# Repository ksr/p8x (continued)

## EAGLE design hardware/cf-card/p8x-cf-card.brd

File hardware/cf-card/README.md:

# CF-IDE Card

> **Theory of operation:** [p8x-cf-card-theory.md](p8x-cf-card-theory.md) — deep walkthrough of inputs/outputs, signal flow, and logic.

Adds mass storage: a CompactFlash card running in **8-bit True IDE mode**,
memory-mapped into the I/O page at **$FF10–$FF17**. This is what lets the P8X load
an OS and a filesystem from removable media instead of living entirely in ROM.

> **Rev B (2026-09-19): two drives.** The routed KiCad board in
> [`kicad/`](kicad/README.md) (not yet fabricated) carries a second, fully decoded
> CF drive: drive 0 at `$FF10–$FF17` on header J2, drive 1 at `$FF18–$FF1F` on
> header J5, each with its own 74245 buffer, strobe glue, pull-ups and activity
> LED (master/slave on one channel was rejected as unreliable for True IDE CF).
> **Software follow-up:** the firmware CF driver and the emulator select drive 1
> with the device bit on `$FF10–$FF17`, so drive 1 on this card needs a
> drive-selectable port base first; drive 0 works unchanged. The chip-by-chip text
> below describes the drive-0 circuit.

> This README describes the circuit as actually built in
> [`generators/gen_eagle.py`](../../generators/gen_eagle.py). For the storage
> software stack see [p8x-cf-os-design.md](p8x-cf-os-design.md) and
> [p8xfs-v2-hierarchical.md](p8xfs-v2-hierarchical.md); for bus pins see
> [p8x-bus-definition.md](../backplane/p8x-bus-definition.md).

## Chip inventory

| Ref | Device | Role |
|-----|--------|------|
| U1 | 74245 | Bidirectional data-bus transceiver (P8X bus ↔ CF data) |
| U2 | 7430 | 8-input NAND — I/O page ($FFxx) detector |
| U3 | 74138 | DOE decoder (read enable) |
| U4 | 74138 | DLD decoder (write strobe) |
| U5 | 74HCT14 | Schmitt inverters — strobe/select conditioning |
| U6, U7 | 7410 | 3-input NAND — register/select decode and -IOR/-IOW gating |
| U8 | 74HCT08 | AND glue — chip-select combine, activity LED |
| J2 | 40-pin IDE | CompactFlash / IDE connector |

## How it works

### Address decode ($FF10–$FF17)
U2 (7430) detects the `$FFxx` page. The CF task-file registers occupy
`$FF10–$FF17`; the low address lines A0–A4 select the individual IDE register, and
the 7410 NANDs (U6/U7) combine the page hit with A3/A4 to produce the two True-IDE
chip selects **-CS0** (command block) and **-CS1** (control block). U8 ANDs them
into a single `-CFSEL` "this card is addressed" signal.

### Read / write strobes
DOE code 7 (`-RD`) and DLD code 7 (`-MEMW`) are decoded by U3/U4. Gated with the
clock and `-CFSEL` through U5/U7, they become the IDE bus strobes **-IOR** (I/O
read) and **-IOW** (I/O write) on the connector. These are the standard True-IDE
timing signals the CF card expects.

### Data path
A single **74245** (U1) bridges the P8X data bus and the CF data lines (the low 8
bits — this is 8-bit mode, so the high byte of the IDE 16-bit data path is unused).
Its **direction** follows `-IOR` (read = drive toward the P8X bus) and it is
**enabled** only when the card is selected (`-CFOE`), so it never contends with
other bus drivers.

### Status lines
The CF's open-drain status lines — **IORDY**, **-PDIAG**, **-DASP** — are pulled up
through a SIP resistor network (RN1). `-DASP` (drive active / slave present) also
drives the activity LED.

### Reset
The backplane **-RES** is wired to the IDE connector's reset pin, so the CF card is
reset together with the rest of the machine.

## Bus codes this card owns
- **DOE:** 7 = read (drives D0–D7 when `$FF10–$FF17` is addressed)
- **DLD:** 7 = write (`MEMW`) — shared decode convention with memory & I/O cards

The CF card, memory card, and I/O card all decode the same DOE=7 / DLD=7 codes;
the address decode (which page/region) is what keeps exactly one of them active per
cycle.

## LEDs
PWR (green), ACT (yellow — card selected / access in progress), DASP (green — CF
present and active).

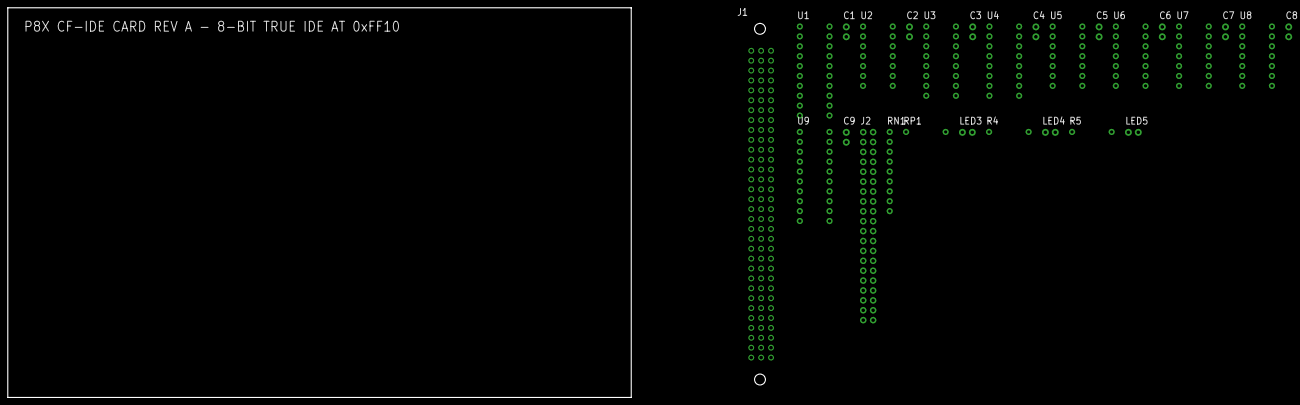
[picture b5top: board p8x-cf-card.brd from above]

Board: 4 copper layers, 160.0 x 100.0 mm, 27 parts (0 on the bottom side), 70 nets, no tracks yet.

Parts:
C1, C2, C3, C4, C5, C6, C7, C8, C9: 100nF; C_DISC1
J1: MABC96R
J2: IDE-40; HDR40
LED3, LED5: GRN; LED5
LED4: YEL; LED5
R4: 1K; R_AXIAL
R5: 330R; R_AXIAL
RN1: 8X10K; SIP9
RP1: 1K; R_AXIAL
U1: 74HCT245; DIP20
U2: 74HCT30; DIP14
U3, U4: 74HCT138; DIP16
U5: 74HCT14; DIP14
U6, U7: 74HCT10; DIP14
U8: 74HCT08; DIP14
U9: 74HCT374; DIP20

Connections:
-CFOE: U1.19, U8.6, U8.9, U8.10
-CFSEL: U5.11, U8.3
-CS0: J2.37, U6.12, U8.1
-CS1: J2.38, U6.6, U8.2
-DASP: J2.39, LED5.1, RN1.4
-IOR: J2.25, U1.1, U7.12, U8.4
-IOW: J2.23, U7.6, U8.5
-MEMW: U4.7, U5.5
-PDIAG: J2.34, RN1.3
-RD: U3.7, U5.3
-RES: J1.A11, J2.1
A0: J1.C3, J2.35
A1: J1.C4, J2.33
A2: J1.C5, J2.36
A3: J1.C6, U5.9, U6.5
A3N: U5.8, U6.13
A4: J1.C7, U6.2, U6.4
A8: J1.C11, U2.1
A9: J1.C12, U2.2
A10: J1.C13, U2.3
A11: J1.C14, U2.4
A12: J1.C15, U2.5
A13: J1.C16, U2.6
A14: J1.C17, U2.11
A15: J1.C18, U2.12
ACTK: LED4.1, U8.8
CFD0: J2.17, U1.18
CFD1: J2.15, U1.17
CFD2: J2.13, U1.16
CFD3: J2.11, U1.15
CFD4: J2.9, U1.14
CFD5: J2.7, U1.13
CFD6: J2.5, U1.12
CFD7: J2.3, U1.11
CFD8: J2.4, U9.3
CFD9: J2.6, U9.4
CFD10: J2.8, U9.7
CFD11: J2.10, U9.8
CFD12: J2.12, U9.13
CFD13: J2.14, U9.14
CFD14: J2.16, U9.17
CFD15: J2.18, U9.18
CLKB: J1.A25, U7.5, U7.13
D0: J1.A3, U1.2
D1: J1.A4, U1.3
D2: J1.A5, U1.4
D3: J1.A6, U1.5
D4: J1.A7, U1.6
D5: J1.A8, U1.7
D6: J1.A9, U1.8
D7: J1.A10, U1.9
DLD0: J1.A16, U4.1
DLD1: J1.A17, U4.2
DLD2: J1.A18, U4.3
DLD3: J1.A19, U4.4
DOE0: J1.A12, U3.1
DOE1: J1.A13, U3.2
DOE2: J1.A14, U3.3
DOE3: J1.A15, U3.4
GND: C1.2, C2.2, C3.2, C4.2, C5.2, C6.2, C7.2, C8.2, C9.2, J1.A31, J1.A32, J1.B3, J1.B5, J1.B7, J1.B9, J1.B11, J1.B13, J1.B15, J1.B17, J1.B19, J1.B21, J1.B23, J1.B25, J1.B31, J1.B32, J1.C31, J1.C32, J2.2, J2.19, J2.22, J2.24, J2.26, J2.28, J2.30, J2.40, LED3.1, U1.10, U2.7, U3.5, U3.8, U4.5, U4.8, U5.7, U5.13, U6.7, U6.9, U6.10, U6.11, U7.7, U7.9, U7.10, U7.11, U8.7, U8.12, U8.13, U9.10, U9.11
IOPG: U2.8, U5.1
IOPGP: U5.2, U6.1, U6.3
IORDY: J2.27, RN1.2
LEDAC: LED4.2, R4.2
LEDDA: LED5.2, R5.2
LEDP: LED3.2, RP1.2
RDP: U5.4, U7.2
SELP: U5.10, U7.1, U7.3
VCC: C1.1, C2.1, C3.1, C4.1, C5.1, C6.1, C7.1, C8.1, C9.1, J1.A1, J1.A2, J1.B1, J1.B2, J1.C1, J1.C2, J2.29, R4.1, R5.1, RN1.1, RP1.1, U1.20, U2.14, U3.6, U3.16, U4.6, U4.16, U5.14, U6.14, U7.14, U8.14, U9.1, U9.20
WRP: U5.6, U7.4

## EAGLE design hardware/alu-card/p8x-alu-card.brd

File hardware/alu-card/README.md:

# ALU Card

> **Theory of operation:** [p8x-alu-card-theory.md](p8x-alu-card-theory.md) — deep walkthrough of inputs/outputs, signal flow, and logic.

Holds the two ALU operand registers (**A**, **B**), the two hidden microcode
temporaries (**T**, **T2**), the **74181-based ALU** with a post-ALU shifter, and
the **FLAGS** register. All arithmetic and logic happens here.

> This README describes the circuit as actually built in
> [`generators/gen_eagle.py`](../../generators/gen_eagle.py). See
> [p8x-system-design.md §5](../../docs/p8x-system-design.md) for the overview and
> [p8x-bus-definition.md](../backplane/p8x-bus-definition.md) for bus pins.

## Chip inventory

| Ref | Device | Role |
|-----|--------|------|
| U1, U2 | 74377 + 74244 | A register (load latch + bus-drive buffer) |
| U3, U4 | 74377 + 74244 | B register |
| U5, U6 | 74377 + 74244 | T register (hidden temp) |
| U7, U8 | 74377 + 74244 | T2 register (hidden temp) |
| U9, U10 | 74181 | ALU, low and high nibble |
| U11 | 74182 | Carry-lookahead generator across the two 74181s |
| U12–U15 | 74157 | Two-stage shifter (pass / <<1 / >>1) |
| U16 | 74244 | ALU-result bus driver |
| U17 | 74175 | FLAGS register (C, Z, N, V) |
| U18 | 74260 | Zero-detect NOR over the result |
| U19 | 74HCT08 | AND glue (zero combine, flag-clock gate) |
| U20 | 74138 | DOE decoder (codes 1–6) |
| U21 | 74138 | DLD decoder (codes 1–5) |
| U22 | 74157 | Flag mux — select computed flags vs restore-from-bus |
| U23 | 74244 | FLAGS → data bus driver |
| U24, U25 | 74HCT32 / 74HCT00 | Flag-load and restore gating |

## How it works

### The four registers
A, B, T, T2 are each a **74377** (8-bit latch with a load enable) paired with a
**74244** output buffer. The 74377 loads from the data bus when its DLD code is
decoded by U21 (`-LDA`/`-LDB`/`-LDT`/`-LDT2`). The 74244 drives the register's value
back onto the data bus when its DOE code is decoded by U20. A and B also feed the
74181 inputs directly and continuously — they don't need to be on the bus for the
ALU to operate on them.

### The ALU (74181 + 74182)
Two 74181s (U9 low nibble, U10 high nibble) form the 8-bit ALU. Function is set by
the backplane lines **ALUS0–3** (operation select), **ALUM** (logic vs arithmetic),
and **CIN** (carry in). Instead of rippling carry between the two 74181s, the
**74182** carry-lookahead generator (U11) takes their propagate/generate outputs
(`!P`/`!G`) and produces the fast intermediate carry `CNX` into the high nibble —
keeping the carry chain short and fast.

> **Carry flag polarity quirk:** the C flag latches the *raw* 74181 `Cn+4` pin,
> which is **active-low** (C=1 means *no* carry out). This is deliberate and the
> emulator reproduces it faithfully — do not "fix" it. See
> [p8x-bus-definition.md §3.8](../backplane/p8x-bus-definition.md).

### The shifter
Two stages of 74157 muxes (U12/U13 then U14/U15) sit after the ALU, selected by
**SH0/SH1**, giving pass-through, shift-left, or shift-right. The shift-in bit is
wired to CIN. The shifted result is driven onto the data bus by U16 (74244) when
DOE selects the ALU result (code 5).

### Flags
- **Z** (zero): U18 (74260) NORs the result bits, combined in U19 — asserted when
  the whole 8-bit result is zero.
- **N** (negative): bit 7 of the result.
- **C** (carry): the raw 74181 `Cn+4` (see quirk above).
- **V** (overflow): **hardwired 0 in rev A** — unimplemented (see BACKLOG).

The 74175 (U17) latches all four flags, but **only when LDF is asserted** (the flag
clock is gated by U19/U24 so non-ALU cycles don't disturb the flags). The U22 74157
mux lets FLAGS be either freshly computed *or* restored from the data bus (DLD
code 5, for PLP-style flag pops), and U23 (74244) drives FLAGS onto the bus for
PHP-style pushes (DOE code 6).

## Bus codes this card owns
- **DOE:** 1=A, 2=B, 3=T, 4=T2, 5=ALU result, 6=FLAGS
- **DLD:** 1=A, 2=B, 3=T, 4=T2, 5=FLAGS (restore)

## LEDs
PWR (green), ALU (green — result on bus), LDF (yellow — flags latching).

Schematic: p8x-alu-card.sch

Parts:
C1, C2, C3, C4, C5, C6, C7, C8, C9, C10, C11, C12, C13, C14, C15, C16, C17, C18, C19, C20, C21, C22, C23, C24, C25, C26, C27, C28, C29, C30, C31, C32, C33, C34, C35: 100nF; C_DISC1
J1: MABC96R
LED3, LED4: GRN; LED5
LED5: YEL; LED5
R4, R5: 1K; R_AXIAL
RP1: 1K; R_AXIAL
U1, U3, U5, U7: 74HCT377; DIP20
U2, U4, U6, U8, U16, U23: 74HCT244; DIP20
U9, U10: 74HCT181; DIP24W
U11: 74HCT182; DIP16
U12, U13, U14, U15, U22, U28, U29, U30, U32, U33: 74HCT157; DIP16
U17: FLAGS; DIP16
U18, U27: 74HCT260; DIP14
U19, U31, U35: 74HCT08; DIP14
U20, U21: 74HCT138; DIP16
U24: 74HCT32; DIP14
U25: 74HCT00; DIP14
U26: 74HCT74; DIP14
U34: 74HCT86; DIP14

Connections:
-CCLR: U26.1 (!1CLR), U31.8 (3Y)
-CLRCb: U25.11 (4Y), U31.10 (3B)
-DOEA: U2.1 (!G1), U2.19 (!G2), U20.14 (Y1)
-DOEALU: U16.1 (!G1), U16.19 (!G2), U19.9 (3A), U19.10 (3B), U20.10 (Y5)
-DOEB: U4.1 (!G1), U4.19 (!G2), U20.13 (Y2)
-DOEFLG: U20.9 (Y6), U23.1 (!G1)
-DOET: U6.1 (!G1), U6.19 (!G2), U20.12 (Y3)
-DOET2: U8.1 (!G1), U8.19 (!G2), U20.11 (Y4)
-LDA: U1.1 (!E), U21.14 (Y1)
-LDB: U3.1 (!E), U21.13 (Y2)
-LDT: U5.1 (!E), U21.12 (Y3)
-LDT2: U7.1 (!E), U21.11 (Y4)
-RES: J1.A11, U17.1 (!CLR), U31.9 (3A)
-SETCb: U25.3 (1Y), U26.4 (!1PRE)
ALUK: LED4.1 (K), U19.8 (3Y)
ALUM: J1.C23, U9.8 (M), U10.8 (M)
ALUS0: J1.C19, U9.6 (S0), U10.6 (S0)
ALUS1: J1.C20, U9.5 (S1), U10.5 (S1)
ALUS2: J1.C21, U9.4 (S2), U10.4 (S2), U34.9 (3A)
ALUS3: J1.C22, U9.3 (S3), U10.3 (S3)
AQ0: U1.2 (Q1), U2.2 (A1), U9.2 (A0)
AQ1: U1.5 (Q2), U2.4 (A2), U9.23 (A1)
AQ2: U1.6 (Q3), U2.6 (A3), U9.21 (A2)
AQ3: U1.9 (Q4), U2.8 (A4), U9.19 (A3)
AQ4: U1.12 (Q5), U2.11 (A5), U10.2 (A0)
AQ5: U1.15 (Q6), U2.13 (A6), U10.23 (A1)
AQ6: U1.16 (Q7), U2.15 (A7), U10.21 (A2)
AQ7: U1.19 (Q8), U2.17 (A8), U10.19 (A3), U34.1 (1A), U34.4 (2A)
BMX0: U9.1 (B0), U32.4 (Y1)
BMX1: U9.22 (B1), U32.7 (Y2)
BMX2: U9.20 (B2), U32.9 (Y3)
BMX3: U9.18 (B3), U32.12 (Y4)
BMX4: U10.1 (B0), U33.4 (Y1)
BMX5: U10.22 (B1), U33.7 (Y2)
BMX6: U10.20 (B2), U33.9 (Y3)
BMX7: U10.18 (B3), U33.12 (Y4), U34.5 (2B)
BQ0: U3.2 (Q1), U4.2 (A1), U32.2 (A1)
BQ1: U3.5 (Q2), U4.4 (A2), U32.5 (A2)
BQ2: U3.6 (Q3), U4.6 (A3), U32.11 (A3)
BQ3: U3.9 (Q4), U4.8 (A4), U32.14 (A4)
BQ4: U3.12 (Q5), U4.11 (A5), U33.2 (A1)
BQ5: U3.15 (Q6), U4.13 (A6), U33.5 (A2)
BQ6: U3.16 (Q7), U4.15 (A7), U33.11 (A3)
BQ7: U3.19 (Q8), U4.17 (A8), U33.14 (A4)
BSEL: J1.B28, U32.1 (S), U33.1 (S)
CFLG: U10.16 (CN4), U25.4 (2A), U25.5 (2B)
CFLGI: U25.6 (2Y), U29.2 (A1)
CG0: U9.17 (!G), U11.3 (!G0)
CG1: U10.17 (!G), U11.1 (!G1)
CIN: J1.C24, U9.7 (CN), U11.13 (CN), U30.2 (A1)
CLK: J1.A24, U1.11 (CLK), U3.11 (CLK), U5.11 (CLK), U7.11 (CLK), U31.1 (1A), U31.5 (2B)
CLKFC: U26.3 (1CLK), U31.3 (1Y)
CLKFZN: U17.9 (CLK), U31.6 (2Y)
CLRC: J1.B27, U25.12 (4A), U25.13 (4B)
CNX: U10.7 (CN), U11.12 (CNX)
CP0: U9.15 (!P), U11.4 (!P0)
CP1: U10.15 (!P), U11.2 (!P1)
D0: J1.A3, U1.3 (D1), U2.18 (Y1), U3.3 (D1), U4.18 (Y1), U5.3 (D1), U6.18 (Y1), U7.3 (D1), U8.18 (Y1), U16.18 (Y1), U23.18 (Y1), U27.1 (A1)
D1: J1.A4, U1.4 (D2), U2.16 (Y2), U3.4 (D2), U4.16 (Y2), U5.4 (D2), U6.16 (Y2), U7.4 (D2), U8.16 (Y2), U16.16 (Y2), U23.16 (Y2), U27.2 (B1)
D2: J1.A5, U1.7 (D3), U2.14 (Y3), U3.7 (D3), U4.14 (Y3), U5.7 (D3), U6.14 (Y3), U7.7 (D3), U8.14 (Y3), U16.14 (Y3), U23.14 (Y3), U27.11 (C1)
D3: J1.A6, U1.8 (D4), U2.12 (Y4), U3.8 (D4), U4.12 (Y4), U5.8 (D4), U6.12 (Y4), U7.8 (D4), U8.12 (Y4), U16.12 (Y4), U23.12 (Y4), U27.12 (D1)
D4: J1.A7, U1.13 (D5), U2.9 (Y5), U3.13 (D5), U4.9 (Y5), U5.13 (D5), U6.9 (Y5), U7.13 (D5), U8.9 (Y5), U16.9 (Y5), U27.13 (E1)
D5: J1.A8, U1.14 (D6), U2.7 (Y6), U3.14 (D6), U4.7 (Y6), U5.14 (D6), U6.7 (Y6), U7.14 (D6), U8.7 (Y6), U16.7 (Y6), U27.3 (A2)
D6: J1.A9, U1.17 (D7), U2.5 (Y7), U3.17 (D7), U4.5 (Y7), U5.17 (D7), U6.5 (Y7), U7.17 (D7), U8.5 (Y7), U16.5 (Y7), U27.4 (B2)
D7: J1.A10, U1.18 (D8), U2.3 (Y8), U3.18 (D8), U4.3 (Y8), U5.18 (D8), U6.3 (Y8), U7.18 (D8), U8.3 (Y8), U16.3 (Y8), U22.6 (B2), U27.5 (C2)
DLD0: J1.A16, U21.1 (A)
DLD1: J1.A17, U21.2 (B)
DLD2: J1.A18, U21.3 (C)
DLD3: J1.A19, U21.4 (!G2A)
DOE0: J1.A12, U20.1 (A)
DOE1: J1.A13, U20.2 (B)
DOE2: J1.A14, U20.3 (C)
DOE3: J1.A15, U20.4 (!G2A)
F0: U9.9 (F0), U12.2 (A1), U12.6 (B2), U28.2 (A1)
F1: U9.10 (F1), U12.5 (A2), U12.10 (B3)
F2: U9.11 (F2), U12.11 (A3), U12.13 (B4)
F3: U9.13 (F3), U12.14 (A4), U13.3 (B1)
F4: U10.9 (F0), U13.2 (A1), U13.6 (B2)
F5: U10.10 (F1), U13.5 (A2), U13.10 (B3)
F6: U10.11 (F2), U13.11 (A3), U13.13 (B4)
F7: U10.13 (F3), U13.14 (A4), U28.3 (B1), U34.2 (1B)
FC: J1.A27, U23.9 (Y5)
FENZN: U24.3 (1Y), U31.4 (2A)
FN: J1.A29, U23.5 (Y7)
FQC: U23.2 (A1), U23.11 (A5), U26.5 (1Q), U30.3 (B1)
FQN: U17.7 (Q2), U23.6 (A3), U23.15 (A7)
FQV: U17.10 (Q3), U23.8 (A4), U23.17 (A8)
FQZ: U17.2 (Q1), U23.4 (A2), U23.13 (A6)
FV: J1.A30, U23.3 (Y8)
FZ: J1.A28, U23.7 (Y6)
G0: U12.4 (Y1), U14.2 (A1)
G1: U12.7 (Y2), U14.3 (B1), U14.5 (A2)
G2: U12.9 (Y3), U14.6 (B2), U14.11 (A3)
G3: U12.12 (Y4), U14.10 (B3), U14.14 (A4)
G4: U13.4 (Y1), U14.13 (B4), U15.2 (A1)
G5: U13.7 (Y2), U15.3 (B1), U15.5 (A2)
G6: U13.9 (Y3), U15.6 (B2), U15.11 (A3)
G7: U13.12 (Y4), U15.10 (B3), U15.14 (A4)
GND: C1.2, C2.2, C3.2, C4.2, C5.2, C6.2, C7.2, C8.2, C9.2, C10.2, C11.2, C12.2, C13.2, C14.2, C15.2, C16.2, C17.2, C18.2, C19.2, C20.2, C21.2, C22.2, C23.2, C24.2, C25.2, C26.2, C27.2, C28.2, C29.2, C30.2, C31.2, C32.2, C33.2, C34.2, C35.2, J1.A31, J1.A32, J1.B3, J1.B5, J1.B7, J1.B9, J1.B11, J1.B13, J1.B15, J1.B17, J1.B19, J1.B21, J1.B23, J1.B25, J1.B31, J1.B32, J1.C31, J1.C32, LED3.1 (K), U1.10 (GND), U2.10 (GND), U3.10 (GND), U4.10 (GND), U5.10 (GND), U6.10 (GND), U7.10 (GND), U8.10 (GND), U9.12 (GND), U10.12 (GND), U11.8 (GND), U12.8 (GND), U12.15 (!G), U13.8 (GND), U13.15 (!G), U14.8 (GND), U14.15 (!G), U15.8 (GND), U15.15 (!G), U16.10 (GND), U17.8 (GND), U18.7 (GND), U18.9 (D2), U18.10 (E2), U19.7 (GND), U19.12 (4A), U19.13 (4B), U20.5 (!G2B), U20.8 (GND), U21.5 (!G2B), U21.8 (GND), U22.8 (GND), U22.15 (!G), U23.10 (GND), U23.19 (!G2), U24.7 (GND), U24.9 (3A), U24.10 (3B), U24.12 (4A), U24.13 (4B), U25.7 (GND), U26.7 (GND), U26.11 (2CLK), U26.12 (2D), U27.7 (GND), U27.9 (D2), U27.10 (E2), U28.8 (GND), U28.15 (!G), U29.8 (GND), U29.15 (!G), U30.8 (GND), U30.15 (!G), U31.7 (GND), U31.12 (4A), U31.13 (4B), U32.8 (GND), U32.15 (!G), U33.8 (GND), U33.15 (!G), U34.7 (GND), U35.4 (2A), U35.5 (2B), U35.7 (GND), U35.9 (3A), U35.10 (3B), U35.12 (4A), U35.13 (4B)
LDF: J1.A26, U24.1 (1A), U25.9 (3A), U25.10 (3B), U31.2 (1B)
LDFK: LED5.1 (K), U25.8 (3Y)
LDZN: J1.C28, U22.1 (S), U24.2 (1B)
LEDAL: LED4.2 (A), R4.2
LEDLF: LED5.2 (A), R5.2
LEDP: LED3.2 (A), RP1.2
NC: U26.2 (1D), U29.4 (Y1)
NS2: U34.8 (3Y), U34.13 (4B)
NSRC: U17.5 (D2), U22.7 (Y2)
R0: U14.4 (Y1), U16.2 (A1), U18.1 (A1)
R1: U14.7 (Y2), U16.4 (A2), U18.2 (B1)
R2: U14.9 (Y3), U16.6 (A3), U18.11 (C1)
R3: U14.12 (Y4), U16.8 (A4), U18.12 (D1)
R4: U15.4 (Y1), U16.11 (A5), U18.13 (E1)
R5: U15.7 (Y2), U16.13 (A6), U18.3 (A2)
R6: U15.9 (Y3), U16.15 (A7), U18.4 (B2)
R7: U15.12 (Y4), U16.17 (A8), U18.5 (C2), U22.5 (A2)
SETC: J1.C30, U25.1 (1A), U25.2 (1B)
SH0: J1.C25, U12.1 (S), U13.1 (S), U24.4 (2A), U28.1 (S)
SH1: J1.C26, U14.1 (S), U15.1 (S), U24.5 (2B)
SHANY: U24.6 (2Y), U29.1 (S)
SHCIN: J1.C29, U30.1 (S)
SHIN: U12.3 (B1), U15.13 (B4), U30.4 (Y1)
SHOUT: U28.4 (Y1), U29.3 (B1)
T2Q0: U7.2 (Q1), U8.2 (A1)
T2Q1: U7.5 (Q2), U8.4 (A2)
T2Q2: U7.6 (Q3), U8.6 (A3)
T2Q3: U7.9 (Q4), U8.8 (A4)
T2Q4: U7.12 (Q5), U8.11 (A5)
T2Q5: U7.15 (Q6), U8.13 (A6)
T2Q6: U7.16 (Q7), U8.15 (A7)
T2Q7: U7.19 (Q8), U8.17 (A8)
TQ0: U5.2 (Q1), U6.2 (A1), U32.3 (B1)
TQ1: U5.5 (Q2), U6.4 (A2), U32.6 (B2)
TQ2: U5.6 (Q3), U6.6 (A3), U32.10 (B3)
TQ3: U5.9 (Q4), U6.8 (A4), U32.13 (B4)
TQ4: U5.12 (Q5), U6.11 (A5), U33.3 (B1)
TQ5: U5.15 (Q6), U6.13 (A6), U33.6 (B2)
TQ6: U5.16 (Q7), U6.15 (A7), U33.10 (B3)
TQ7: U5.19 (Q8), U6.17 (A8), U33.13 (B4)
VCC: C1.1, C2.1, C3.1, C4.1, C5.1, C6.1, C7.1, C8.1, C9.1, C10.1, C11.1, C12.1, C13.1, C14.1, C15.1, C16.1, C17.1, C18.1, C19.1, C20.1, C21.1, C22.1, C23.1, C24.1, C25.1, C26.1, C27.1, C28.1, C29.1, C30.1, C31.1, C32.1, C33.1, C34.1, C35.1, J1.A1, J1.A2, J1.B1, J1.B2, J1.C1, J1.C2, R4.1, R5.1, RP1.1, U1.20 (VCC), U2.20 (VCC), U3.20 (VCC), U4.20 (VCC), U5.20 (VCC), U6.20 (VCC), U7.20 (VCC), U8.20 (VCC), U9.24 (VCC), U10.24 (VCC), U11.5 (!G3), U11.6 (!P3), U11.14 (!P2), U11.15 (!G2), U11.16 (VCC), U12.16 (VCC), U13.16 (VCC), U14.16 (VCC), U15.16 (VCC), U16.20 (VCC), U17.16 (VCC), U18.14 (VCC), U19.14 (VCC), U20.6 (G1), U20.16 (VCC), U21.6 (G1), U21.16 (VCC), U22.16 (VCC), U23.20 (VCC), U24.14 (VCC), U25.14 (VCC), U26.10 (!2PRE), U26.13 (!2CLR), U26.14 (VCC), U27.14 (VCC), U28.16 (VCC), U29.16 (VCC), U30.16 (VCC), U31.14 (VCC), U32.16 (VCC), U33.16 (VCC), U34.10 (3B), U34.14 (VCC), U35.14 (VCC)
VSRC: U17.12 (D3), U35.3 (1Y)
VX1: U34.3 (1Y), U35.1 (1A)
VX2: U34.6 (2Y), U34.12 (4A)
VX4: U34.11 (4Y), U35.2 (1B)
ZBH: U19.5 (2B), U27.6 (Y2)
ZBL: U19.4 (2A), U27.8 (Y1)
ZBUS: U19.6 (2Y), U22.3 (B1)
ZFLG: U19.3 (1Y), U22.2 (A1)
ZH: U18.6 (Y2), U19.2 (1B)
ZL: U18.8 (Y1), U19.1 (1A)
ZSRC: U17.4 (D1), U22.4 (Y1)

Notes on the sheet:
P8X ALU CARD REV B (conventional carry, LDZN, SETC/CLRC, carry-coupled shifter)
CLK/FORCE GATES
74HCT08
V XOR
74HCT86
V AND
A REG
74HCT377
A OUT
74HCT244
B REG
B OUT
T REG
T OUT
T2 REG
T2 OUT
ALU LO
74HCT181
ALU HI
CLA
74HCT182
SH1 LO
74HCT157
SH1 HI
SH2 LO
SH2 HI
ALU OUT
Z DET
74HCT260
DOE DEC
74HCT138
DLD DEC
FLAG MUX
FLAG OUT
C FLAG FF
74HCT74
BUS Z-DET
SHIFT-OUT MUX
C-SRC MUX
SHIN MUX

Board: 4 copper layers, 77 parts (0 on the bottom side), 151 nets, no tracks yet.

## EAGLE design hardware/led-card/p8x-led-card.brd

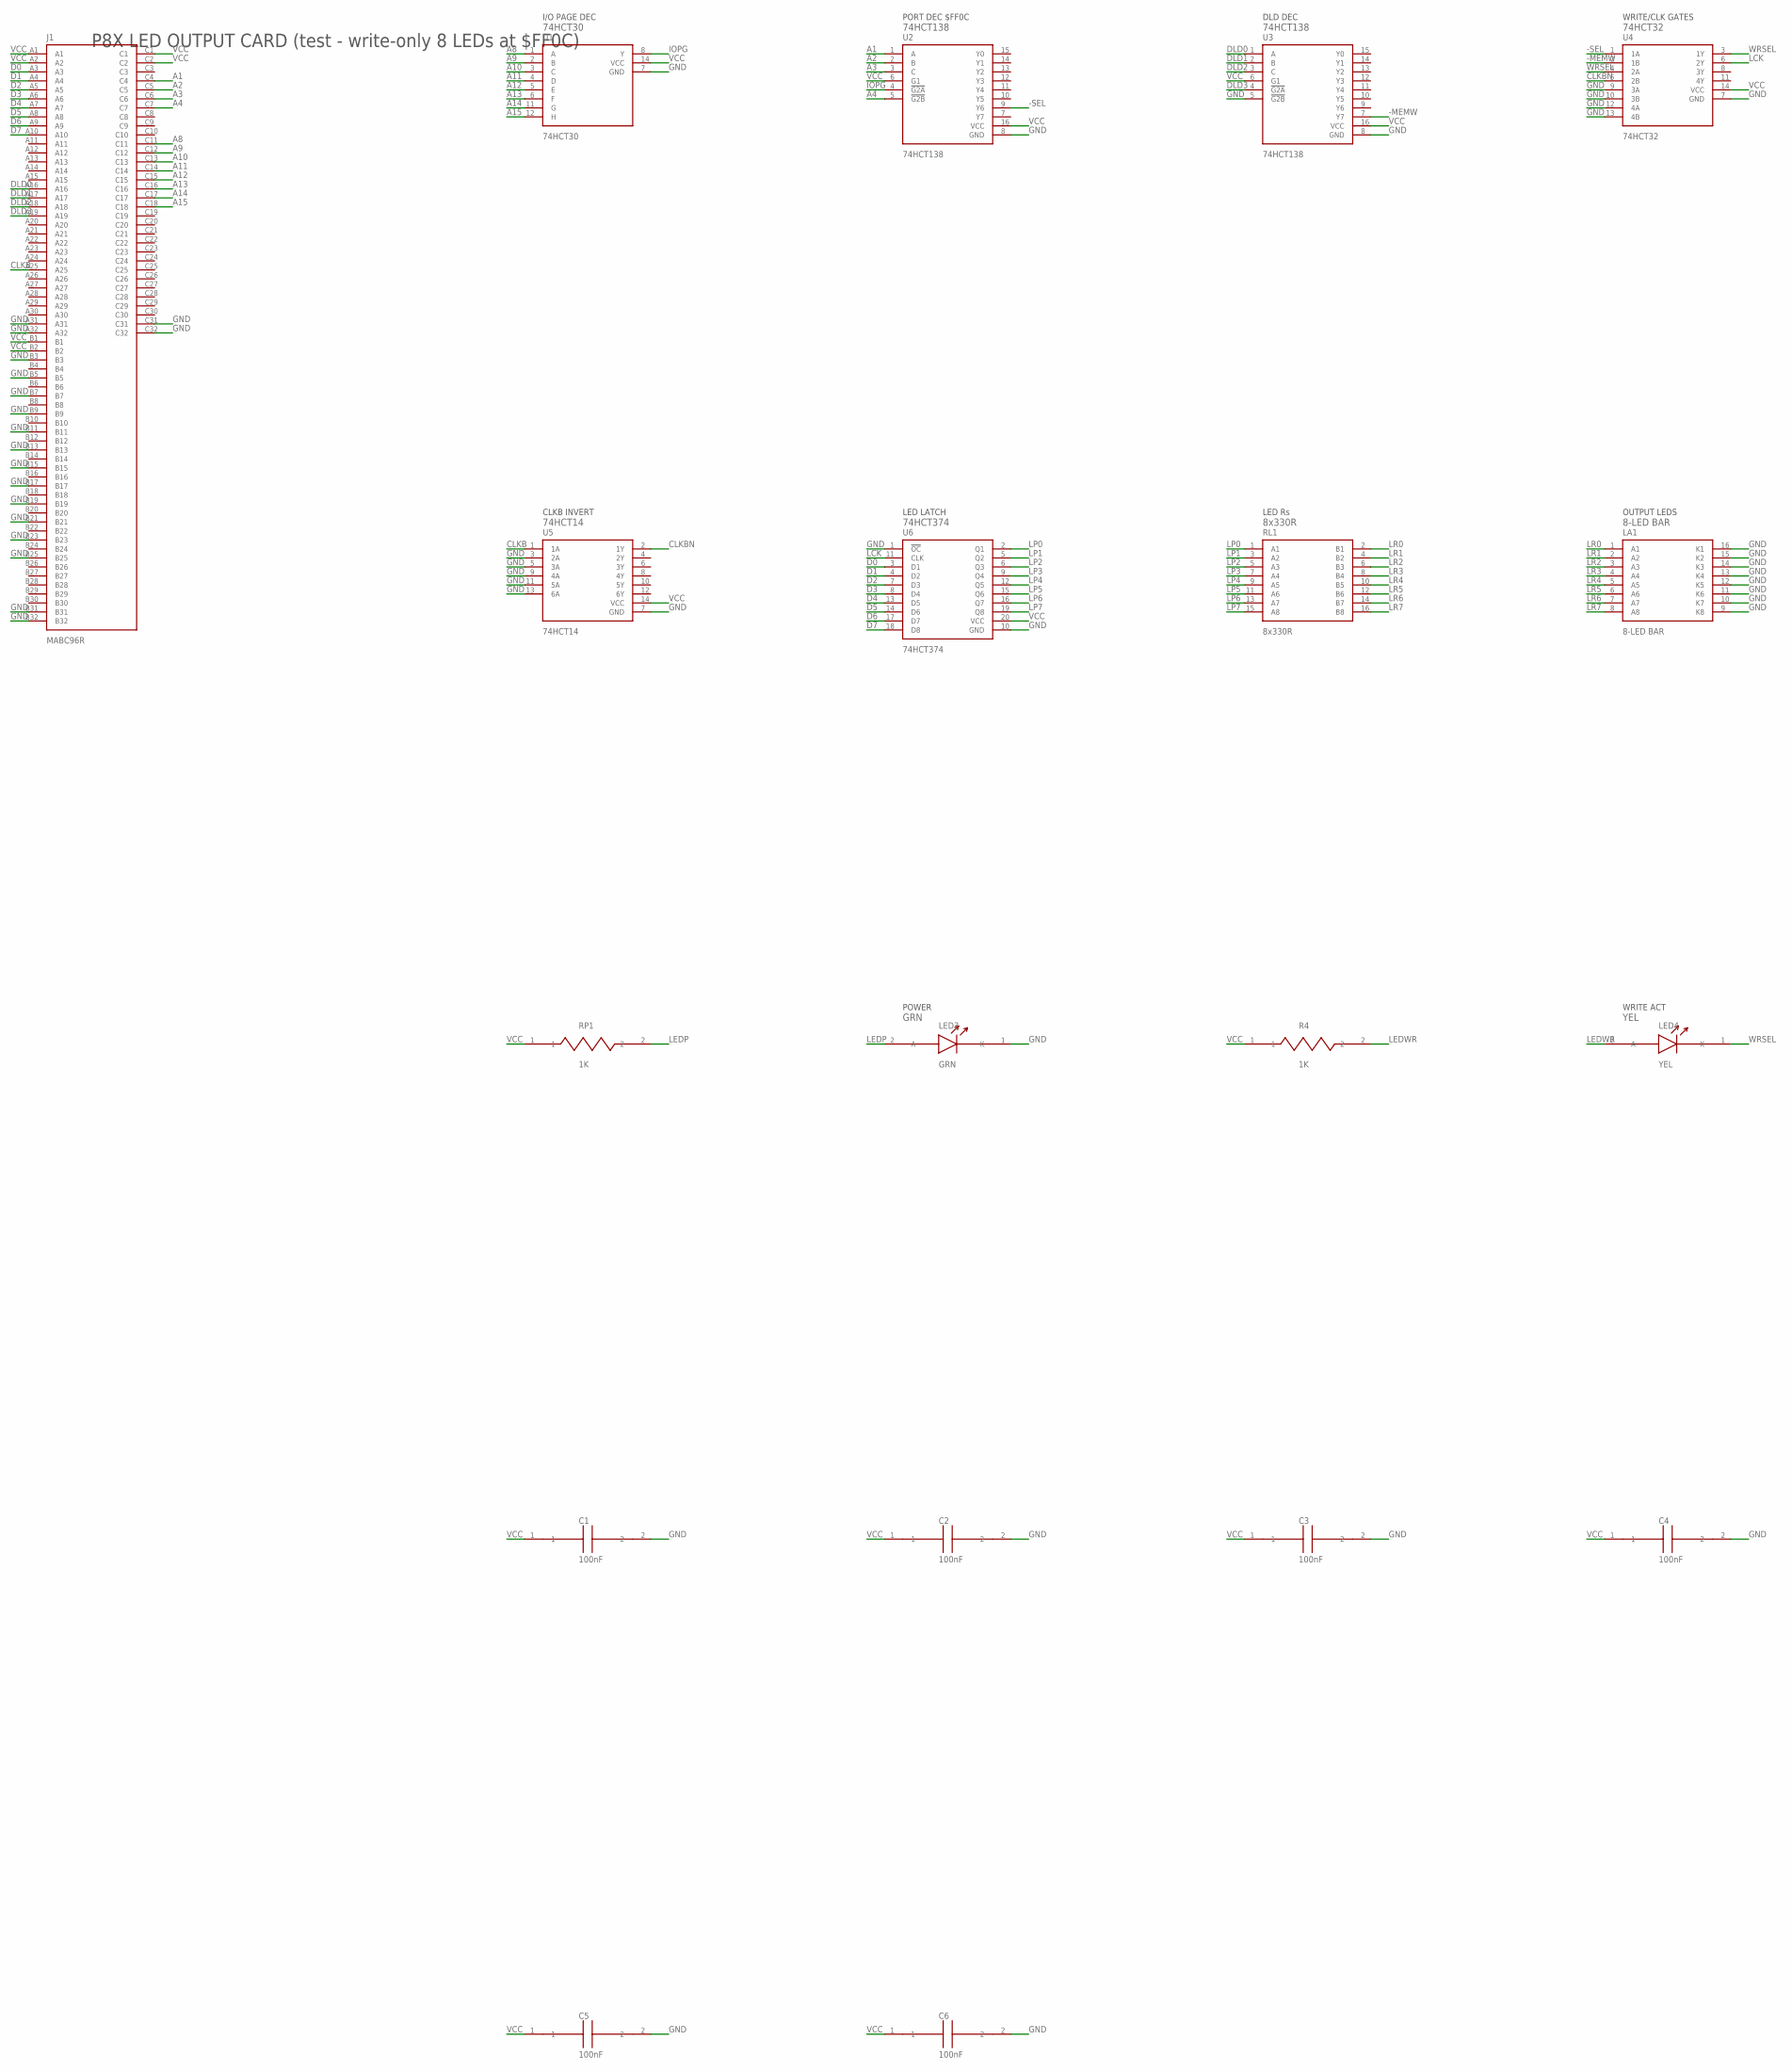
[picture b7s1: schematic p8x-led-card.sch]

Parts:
C1, C2, C3, C4, C5, C6: 100nF; C_DISC1
J1: MABC96R
LA1: 8-LED BAR; DIP16
LED3: GRN; LED5
LED4: YEL; LED5
R4: 1K; R_AXIAL
RL1: 8x330R; SIP16
RP1: 1K; R_AXIAL
U1: 74HCT30; DIP14
U2, U3: 74HCT138; DIP16
U4: 74HCT32; DIP14
U5: 74HCT14; DIP14
U6: 74HCT374; DIP20

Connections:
-MEMW: U3.7 (Y7), U4.2 (1B)
-SEL: U2.9 (Y6), U4.1 (1A)
A1: J1.C4, U2.1 (A)
A2: J1.C5, U2.2 (B)
A3: J1.C6, U2.3 (C)
A4: J1.C7, U2.5 (!G2B)
A8: J1.C11, U1.1 (A)
A9: J1.C12, U1.2 (B)
A10: J1.C13, U1.3 (C)
A11: J1.C14, U1.4 (D)
A12: J1.C15, U1.5 (E)
A13: J1.C16, U1.6 (F)
A14: J1.C17, U1.11 (G)
A15: J1.C18, U1.12 (H)
CLKB: J1.A25, U5.1 (1A)
CLKBN: U4.5 (2B), U5.2 (1Y)
D0: J1.A3, U6.3 (D1)
D1: J1.A4, U6.4 (D2)
D2: J1.A5, U6.7 (D3)
D3: J1.A6, U6.8 (D4)
D4: J1.A7, U6.13 (D5)
D5: J1.A8, U6.14 (D6)
D6: J1.A9, U6.17 (D7)
D7: J1.A10, U6.18 (D8)
DLD0: J1.A16, U3.1 (A)
DLD1: J1.A17, U3.2 (B)
DLD2: J1.A18, U3.3 (C)
DLD3: J1.A19, U3.4 (!G2A)
GND: C1.2, C2.2, C3.2, C4.2, C5.2, C6.2, J1.A31, J1.A32, J1.B3, J1.B5, J1.B7, J1.B9, J1.B11, J1.B13, J1.B15, J1.B17, J1.B19, J1.B21, J1.B23, J1.B25, J1.B31, J1.B32, J1.C31, J1.C32, LA1.9 (K8), LA1.10 (K7), LA1.11 (K6), LA1.12 (K5), LA1.13 (K4), LA1.14 (K3), LA1.15 (K2), LA1.16 (K1), LED3.1 (K), U1.7 (GND), U2.8 (GND), U3.5 (!G2B), U3.8 (GND), U4.7 (GND), U4.9 (3A), U4.10 (3B), U4.12 (4A), U4.13 (4B), U5.3 (2A), U5.5 (3A), U5.7 (GND), U5.9 (4A), U5.11 (5A), U5.13 (6A), U6.1 (!OC), U6.10 (GND)
IOPG: U1.8 (Y), U2.4 (!G2A)
LCK: U4.6 (2Y), U6.11 (CLK)
LEDP: LED3.2 (A), RP1.2
LEDWR: LED4.2 (A), R4.2
LP0: RL1.1 (A1), U6.2 (Q1)
LP1: RL1.3 (A2), U6.5 (Q2)
LP2: RL1.5 (A3), U6.6 (Q3)
LP3: RL1.7 (A4), U6.9 (Q4)
LP4: RL1.9 (A5), U6.12 (Q5)
LP5: RL1.11 (A6), U6.15 (Q6)
LP6: RL1.13 (A7), U6.16 (Q7)
LP7: RL1.15 (A8), U6.19 (Q8)
LR0: LA1.1 (A1), RL1.2 (B1)
LR1: LA1.2 (A2), RL1.4 (B2)
LR2: LA1.3 (A3), RL1.6 (B3)
LR3: LA1.4 (A4), RL1.8 (B4)
LR4: LA1.5 (A5), RL1.10 (B5)
LR5: LA1.6 (A6), RL1.12 (B6)
LR6: LA1.7 (A7), RL1.14 (B7)
LR7: LA1.8 (A8), RL1.16 (B8)
VCC: C1.1, C2.1, C3.1, C4.1, C5.1, C6.1, J1.A1, J1.A2, J1.B1, J1.B2, J1.C1, J1.C2, R4.1, RP1.1, U1.14 (VCC), U2.6 (G1), U2.16 (VCC), U3.6 (G1), U3.16 (VCC), U4.14 (VCC), U5.14 (VCC), U6.20 (VCC)
WRSEL: LED4.1 (K), U4.3 (1Y), U4.4 (2A)

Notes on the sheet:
P8X LED OUTPUT CARD (test - write-only 8 LEDs at $FF0C)
I/O PAGE DEC
74HCT30
PORT DEC $FF0C
74HCT138
DLD DEC
WRITE/CLK GATES
74HCT32
CLKB INVERT
74HCT14
LED LATCH
74HCT374
LED Rs
8x330R
OUTPUT LEDS
8-LED BAR
POWER
GRN
WRITE ACT
YEL

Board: 4 copper layers, 19 parts (0 on the bottom side), 51 nets, no tracks yet.

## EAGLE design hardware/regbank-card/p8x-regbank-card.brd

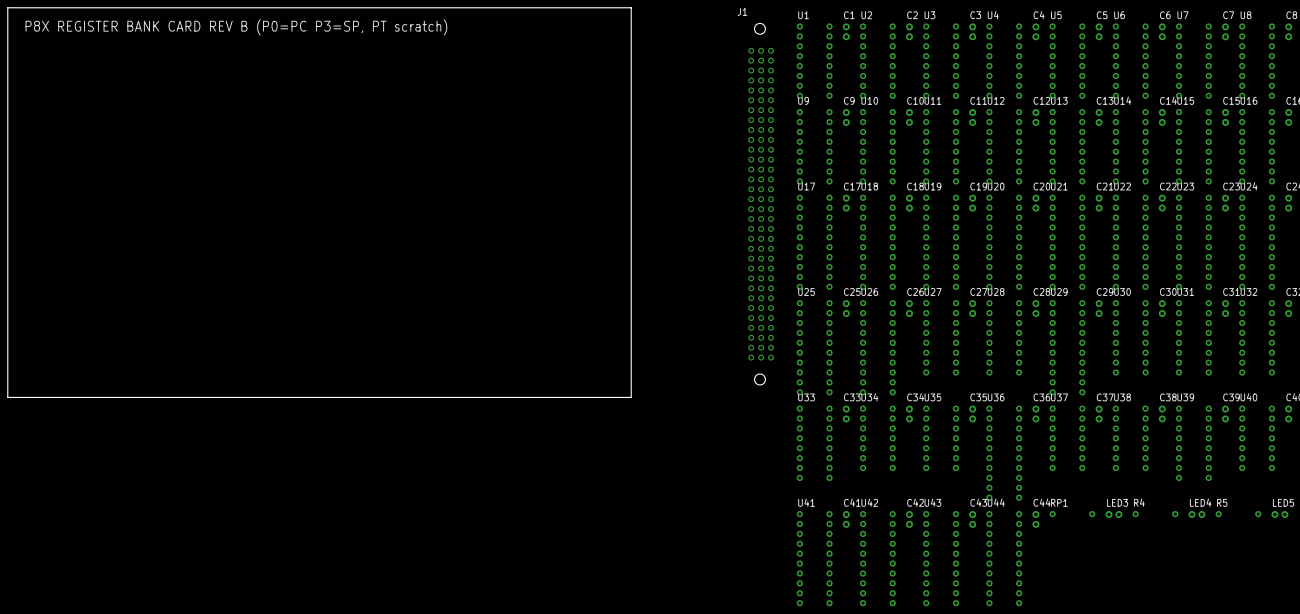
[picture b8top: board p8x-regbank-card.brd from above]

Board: 4 copper layers, 160.0 x 100.0 mm, 95 parts (0 on the bottom side), 194 nets, no tracks yet.

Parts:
C1, C2, C3, C4, C5, C6, C7, C8, C9, C10, C11, C12, C13, C14, C15, C16, C17, C18, C19, C20, C21, C22, C23, C24, C25, C26, C27, C28, C29, C30, C31, C32, C33, C34, C35, C36, C37, C38, C39, C40, C41, C42, C43, C44: 100nF; C_DISC1
J1: MABC96R
LED3, LED4: GRN; LED5
LED5: YEL; LED5
R4, R5: 1K; R_AXIAL
RP1: 1K; R_AXIAL
U1, U2, U3, U4, U5, U6, U7, U8, U9, U10, U11, U12, U13, U14, U15, U16: 74HCT169; DIP16
U17, U18, U19, U20, U21, U22, U23, U24, U25, U26, U29, U36, U43, U44: 74HCT244; DIP20
U27, U28: 74HCT257; DIP16
U30, U31, U33: 74HCT138; DIP16
U32, U39: 74HCT139; DIP16
U34: 74HCT02; DIP14
U35: 74HCT14; DIP14
U37, U38: 74HCT08; DIP14
U40: 74HCT32; DIP14
U41, U42: 74HCT377; DIP20

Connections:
-CNT0: U1.7, U1.10, U2.7, U3.7, U4.7, U39.4
-CNT1: U5.7, U5.10, U6.7, U7.7, U8.7, U39.5
-CNT2: U9.7, U9.10, U10.7, U11.7, U12.7, U39.6
-CNT3: U13.7, U13.10, U14.7, U15.7, U16.7, U39.7
-LDH: U30.14, U37.13, U40.4, U40.12
-LDH0: U32.12, U37.4
-LDH0E: U3.9, U4.9, U37.6
-LDH1: U7.9, U8.9, U32.11
-LDH2: U11.9, U12.9, U32.10
-LDH3: U15.9, U16.9, U32.9
-LDH4: U40.11, U42.1
-LDHG: U32.15, U40.6
-LDL: U30.15, U37.12, U40.1, U40.9
-LDL0: U32.4, U37.1
-LDL0E: U1.9, U2.9, U37.3
-LDL1: U5.9, U6.9, U32.5
-LDL2: U9.9, U10.9, U32.6
-LDL3: U13.9, U14.9, U32.7
-LDL4: U40.8, U41.1
-LDLG: U32.1, U40.3
-LDP: U37.11, U38.4, U38.5
-POE: U29.1, U29.19, U37.8, U38.1, U38.2
-POEH: U31.14, U35.3, U37.10
-POEL: U31.15, U37.9
-RES: J1.A11, U36.1, U36.19, U37.2, U37.5
-SEL0: U17.1, U17.19, U18.1, U18.19, U33.15
-SEL1: U19.1, U19.19, U20.1, U20.19, U33.14
-SEL2: U21.1, U21.19, U22.1, U22.19, U33.13
-SEL3: U23.1, U23.19, U24.1, U24.19, U33.12
-SEL4: U33.11, U40.10, U40.13, U43.1, U43.19, U44.1, U44.19
A0: J1.C3, U25.18
A1: J1.C4, U25.16
A2: J1.C5, U25.14
A3: J1.C6, U25.12
A4: J1.C7, U25.9
A5: J1.C8, U25.7
A6: J1.C9, U25.5
A7: J1.C10, U25.3
A8: J1.C11, U26.18
A9: J1.C12, U26.16
A10: J1.C13, U26.14
A11: J1.C14, U26.12
A12: J1.C15, U26.9
A13: J1.C16, U26.7
A14: J1.C17, U26.5
A15: J1.C18, U26.3
CLK: J1.A24, U1.2, U2.2, U3.2, U4.2, U5.2, U6.2, U7.2, U8.2, U9.2, U10.2, U11.2, U12.2, U13.2, U14.2, U15.2, U16.2, U41.11, U42.11
CNTN: U34.1, U39.1
D0: J1.A3, U1.3, U3.3, U5.3, U7.3, U9.3, U11.3, U13.3, U15.3, U29.18, U36.18, U41.3, U42.3
D1: J1.A4, U1.4, U3.4, U5.4, U7.4, U9.4, U11.4, U13.4, U15.4, U29.16, U36.16, U41.4, U42.4
D2: J1.A5, U1.5, U3.5, U5.5, U7.5, U9.5, U11.5, U13.5, U15.5, U29.14, U36.14, U41.7, U42.7
D3: J1.A6, U1.6, U3.6, U5.6, U7.6, U9.6, U11.6, U13.6, U15.6, U29.12, U36.12, U41.8, U42.8
D4: J1.A7, U2.3, U4.3, U6.3, U8.3, U10.3, U12.3, U14.3, U16.3, U29.9, U36.9, U41.13, U42.13
D5: J1.A8, U2.4, U4.4, U6.4, U8.4, U10.4, U12.4, U14.4, U16.4, U29.7, U36.7, U41.14, U42.14
D6: J1.A9, U2.5, U4.5, U6.5, U8.5, U10.5, U12.5, U14.5, U16.5, U29.5, U36.5, U41.17, U42.17
D7: J1.A10, U2.6, U4.6, U6.6, U8.6, U10.6, U12.6, U14.6, U16.6, U29.3, U36.3, U41.18, U42.18
DLD0: J1.A16, U30.1
DLD1: J1.A17, U30.2
DLD2: J1.A18, U30.3
DLD3: J1.A19, U30.6
DOE0: J1.A12, U31.1
DOE1: J1.A13, U31.2
DOE2: J1.A14, U31.3
DOE3: J1.A15, U31.6
GND: C1.2, C2.2, C3.2, C4.2, C5.2, C6.2, C7.2, C8.2, C9.2, C10.2, C11.2, C12.2, C13.2, C14.2, C15.2, C16.2, C17.2, C18.2, C19.2, C20.2, C21.2, C22.2, C23.2, C24.2, C25.2, C26.2, C27.2, C28.2, C29.2, C30.2, C31.2, C32.2, C33.2, C34.2, C35.2, C36.2, C37.2, C38.2, C39.2, C40.2, C41.2, C42.2, C43.2, C44.2, J1.A31, J1.A32, J1.B3, J1.B5, J1.B7, J1.B9, J1.B11, J1.B13, J1.B15, J1.B17, J1.B19, J1.B21, J1.B23, J1.B25, J1.B31, J1.B32, J1.C31, J1.C32, LED3.1, U1.8, U2.8, U3.8, U4.8, U5.8, U6.8, U7.8, U8.8, U9.8, U10.8, U11.8, U12.8, U13.8, U14.8, U15.8, U16.8, U17.10, U18.10, U19.10, U20.10, U21.10, U22.10, U23.10, U24.10, U25.1, U25.10, U25.19, U26.1, U26.10, U26.19, U27.8, U27.15, U28.8, U28.15, U29.10, U30.4, U30.5, U30.8, U31.4, U31.5, U31.8, U32.8, U33.4, U33.5, U33.8, U34.5, U34.6, U34.7, U34.8, U34.9, U34.11, U34.12, U35.5, U35.7, U35.9, U35.11, U35.13, U36.2, U36.4, U36.6, U36.8, U36.10, U36.11, U36.13, U36.15, U36.17, U37.7, U38.7, U38.9, U38.10, U38.12, U38.13, U39.8, U39.13, U39.14, U40.7, U41.10, U42.10, U43.10, U44.10
LDK: LED5.1, U38.6
LEDLD: LED5.2, R5.2
LEDP: LED3.2, RP1.2
LEDRD: LED4.2, R4.2
PB0: U17.18, U19.18, U21.18, U23.18, U25.2, U27.2, U43.18
PB1: U17.16, U19.16, U21.16, U23.16, U25.4, U27.5, U43.16
PB2: U17.14, U19.14, U21.14, U23.14, U25.6, U27.11, U43.14
PB3: U17.12, U19.12, U21.12, U23.12, U25.8, U27.14, U43.12
PB4: U17.9, U19.9, U21.9, U23.9, U25.11, U28.2, U43.9
PB5: U17.7, U19.7, U21.7, U23.7, U25.13, U28.5, U43.7
PB6: U17.5, U19.5, U21.5, U23.5, U25.15, U28.11, U43.5
PB7: U17.3, U19.3, U21.3, U23.3, U25.17, U28.14, U43.3
PB8: U18.18, U20.18, U22.18, U24.18, U26.2, U27.3, U44.18
PB9: U18.16, U20.16, U22.16, U24.16, U26.4, U27.6, U44.16
PB10: U18.14, U20.14, U22.14, U24.14, U26.6, U27.10, U44.14
PB11: U18.12, U20.12, U22.12, U24.12, U26.8, U27.13, U44.12
PB12: U18.9, U20.9, U22.9, U24.9, U26.11, U28.3, U44.9
PB13: U18.7, U20.7, U22.7, U24.7, U26.13, U28.6, U44.7
PB14: U18.5, U20.5, U22.5, U24.5, U26.15, U28.10, U44.5
PB15: U18.3, U20.3, U22.3, U24.3, U26.17, U28.13, U44.3
PDEC: J1.A23, U34.3, U35.1
PINC: J1.A22, U34.2
POEHP: U27.1, U28.1, U35.4
PQ0_0: U1.14, U17.2
PQ0_1: U1.13, U17.4
PQ0_2: U1.12, U17.6
PQ0_3: U1.11, U17.8
PQ0_4: U2.14, U17.11
PQ0_5: U2.13, U17.13
PQ0_6: U2.12, U17.15
PQ0_7: U2.11, U17.17
PQ0_8: U3.14, U18.2
PQ0_9: U3.13, U18.4
PQ0_10: U3.12, U18.6
PQ0_11: U3.11, U18.8
PQ0_12: U4.14, U18.11
PQ0_13: U4.13, U18.13
PQ0_14: U4.12, U18.15
PQ0_15: U4.11, U18.17
PQ1_0: U5.14, U19.2
PQ1_1: U5.13, U19.4
PQ1_2: U5.12, U19.6
PQ1_3: U5.11, U19.8
PQ1_4: U6.14, U19.11
PQ1_5: U6.13, U19.13
PQ1_6: U6.12, U19.15
PQ1_7: U6.11, U19.17
PQ1_8: U7.14, U20.2
PQ1_9: U7.13, U20.4
PQ1_10: U7.12, U20.6
PQ1_11: U7.11, U20.8
PQ1_12: U8.14, U20.11
PQ1_13: U8.13, U20.13
PQ1_14: U8.12, U20.15
PQ1_15: U8.11, U20.17
PQ2_0: U9.14, U21.2
PQ2_1: U9.13, U21.4
PQ2_2: U9.12, U21.6
PQ2_3: U9.11, U21.8
PQ2_4: U10.14, U21.11
PQ2_5: U10.13, U21.13
PQ2_6: U10.12, U21.15
PQ2_7: U10.11, U21.17
PQ2_8: U11.14, U22.2
PQ2_9: U11.13, U22.4
PQ2_10: U11.12, U22.6
PQ2_11: U11.11, U22.8
PQ2_12: U12.14, U22.11
PQ2_13: U12.13, U22.13
PQ2_14: U12.12, U22.15
PQ2_15: U12.11, U22.17
PQ3_0: U13.14, U23.2
PQ3_1: U13.13, U23.4
PQ3_2: U13.12, U23.6
PQ3_3: U13.11, U23.8
PQ3_4: U14.14, U23.11
PQ3_5: U14.13, U23.13
PQ3_6: U14.12, U23.15
PQ3_7: U14.11, U23.17
PQ3_8: U15.14, U24.2
PQ3_9: U15.13, U24.4
PQ3_10: U15.12, U24.6
PQ3_11: U15.11, U24.8
PQ3_12: U16.14, U24.11
PQ3_13: U16.13, U24.13
PQ3_14: U16.12, U24.15
PQ3_15: U16.11, U24.17
PSEL0: J1.A20, U32.2, U32.14, U33.1, U39.2
PSEL1: J1.A21, U32.3, U32.13, U33.2, U39.3
PSEL2: J1.C27, U33.3, U40.2, U40.5
PTQ0_0: U41.2, U43.2
PTQ0_1: U41.5, U43.4
PTQ0_2: U41.6, U43.6
PTQ0_3: U41.9, U43.8
PTQ0_4: U41.12, U43.11
PTQ0_5: U41.15, U43.13
PTQ0_6: U41.16, U43.15
PTQ0_7: U41.19, U43.17
PTQ1_0: U42.2, U44.2
PTQ1_1: U42.5, U44.4
PTQ1_2: U42.6, U44.6
PTQ1_3: U42.9, U44.8
PTQ1_4: U42.12, U44.11
PTQ1_5: U42.15, U44.13
PTQ1_6: U42.16, U44.15
PTQ1_7: U42.19, U44.17
RB0: U27.4, U29.2
RB1: U27.7, U29.4
RB2: U27.9, U29.6
RB3: U27.12, U29.8
RB4: U28.4, U29.11
RB5: U28.7, U29.13
RB6: U28.9, U29.15
RB7: U28.12, U29.17
RC0_0: U1.15, U2.10
RC0_1: U2.15, U3.10
RC0_2: U3.15, U4.10
RC1_0: U5.15, U6.10
RC1_1: U6.15, U7.10
RC1_2: U7.15, U8.10
RC2_0: U9.15, U10.10
RC2_1: U10.15, U11.10
RC2_2: U11.15, U12.10
RC3_0: U13.15, U14.10
RC3_1: U14.15, U15.10
RC3_2: U15.15, U16.10
RDK: LED4.1, U38.3
UDB: U1.1, U2.1, U3.1, U4.1, U5.1, U6.1, U7.1, U8.1, U9.1, U10.1, U11.1, U12.1, U13.1, U14.1, U15.1, U16.1, U35.2
VCC: C1.1, C2.1, C3.1, C4.1, C5.1, C6.1, C7.1, C8.1, C9.1, C10.1, C11.1, C12.1, C13.1, C14.1, C15.1, C16.1, C17.1, C18.1, C19.1, C20.1, C21.1, C22.1, C23.1, C24.1, C25.1, C26.1, C27.1, C28.1, C29.1, C30.1, C31.1, C32.1, C33.1, C34.1, C35.1, C36.1, C37.1, C38.1, C39.1, C40.1, C41.1, C42.1, C43.1, C44.1, J1.A1, J1.A2, J1.B1, J1.B2, J1.C1, J1.C2, R4.1, R5.1, RP1.1, U1.16, U2.16, U3.16, U4.16, U5.16, U6.16, U7.16, U8.16, U9.16, U10.16, U11.16, U12.16, U13.16, U14.16, U15.16, U16.16, U17.20, U18.20, U19.20, U20.20, U21.20, U22.20, U23.20, U24.20, U25.20, U26.20, U27.16, U28.16, U29.20, U30.16, U31.16, U32.16, U33.6, U33.16, U34.14, U35.14, U36.20, U37.14, U38.14, U39.15, U39.16, U40.14, U41.20, U42.20, U43.20, U44.20
